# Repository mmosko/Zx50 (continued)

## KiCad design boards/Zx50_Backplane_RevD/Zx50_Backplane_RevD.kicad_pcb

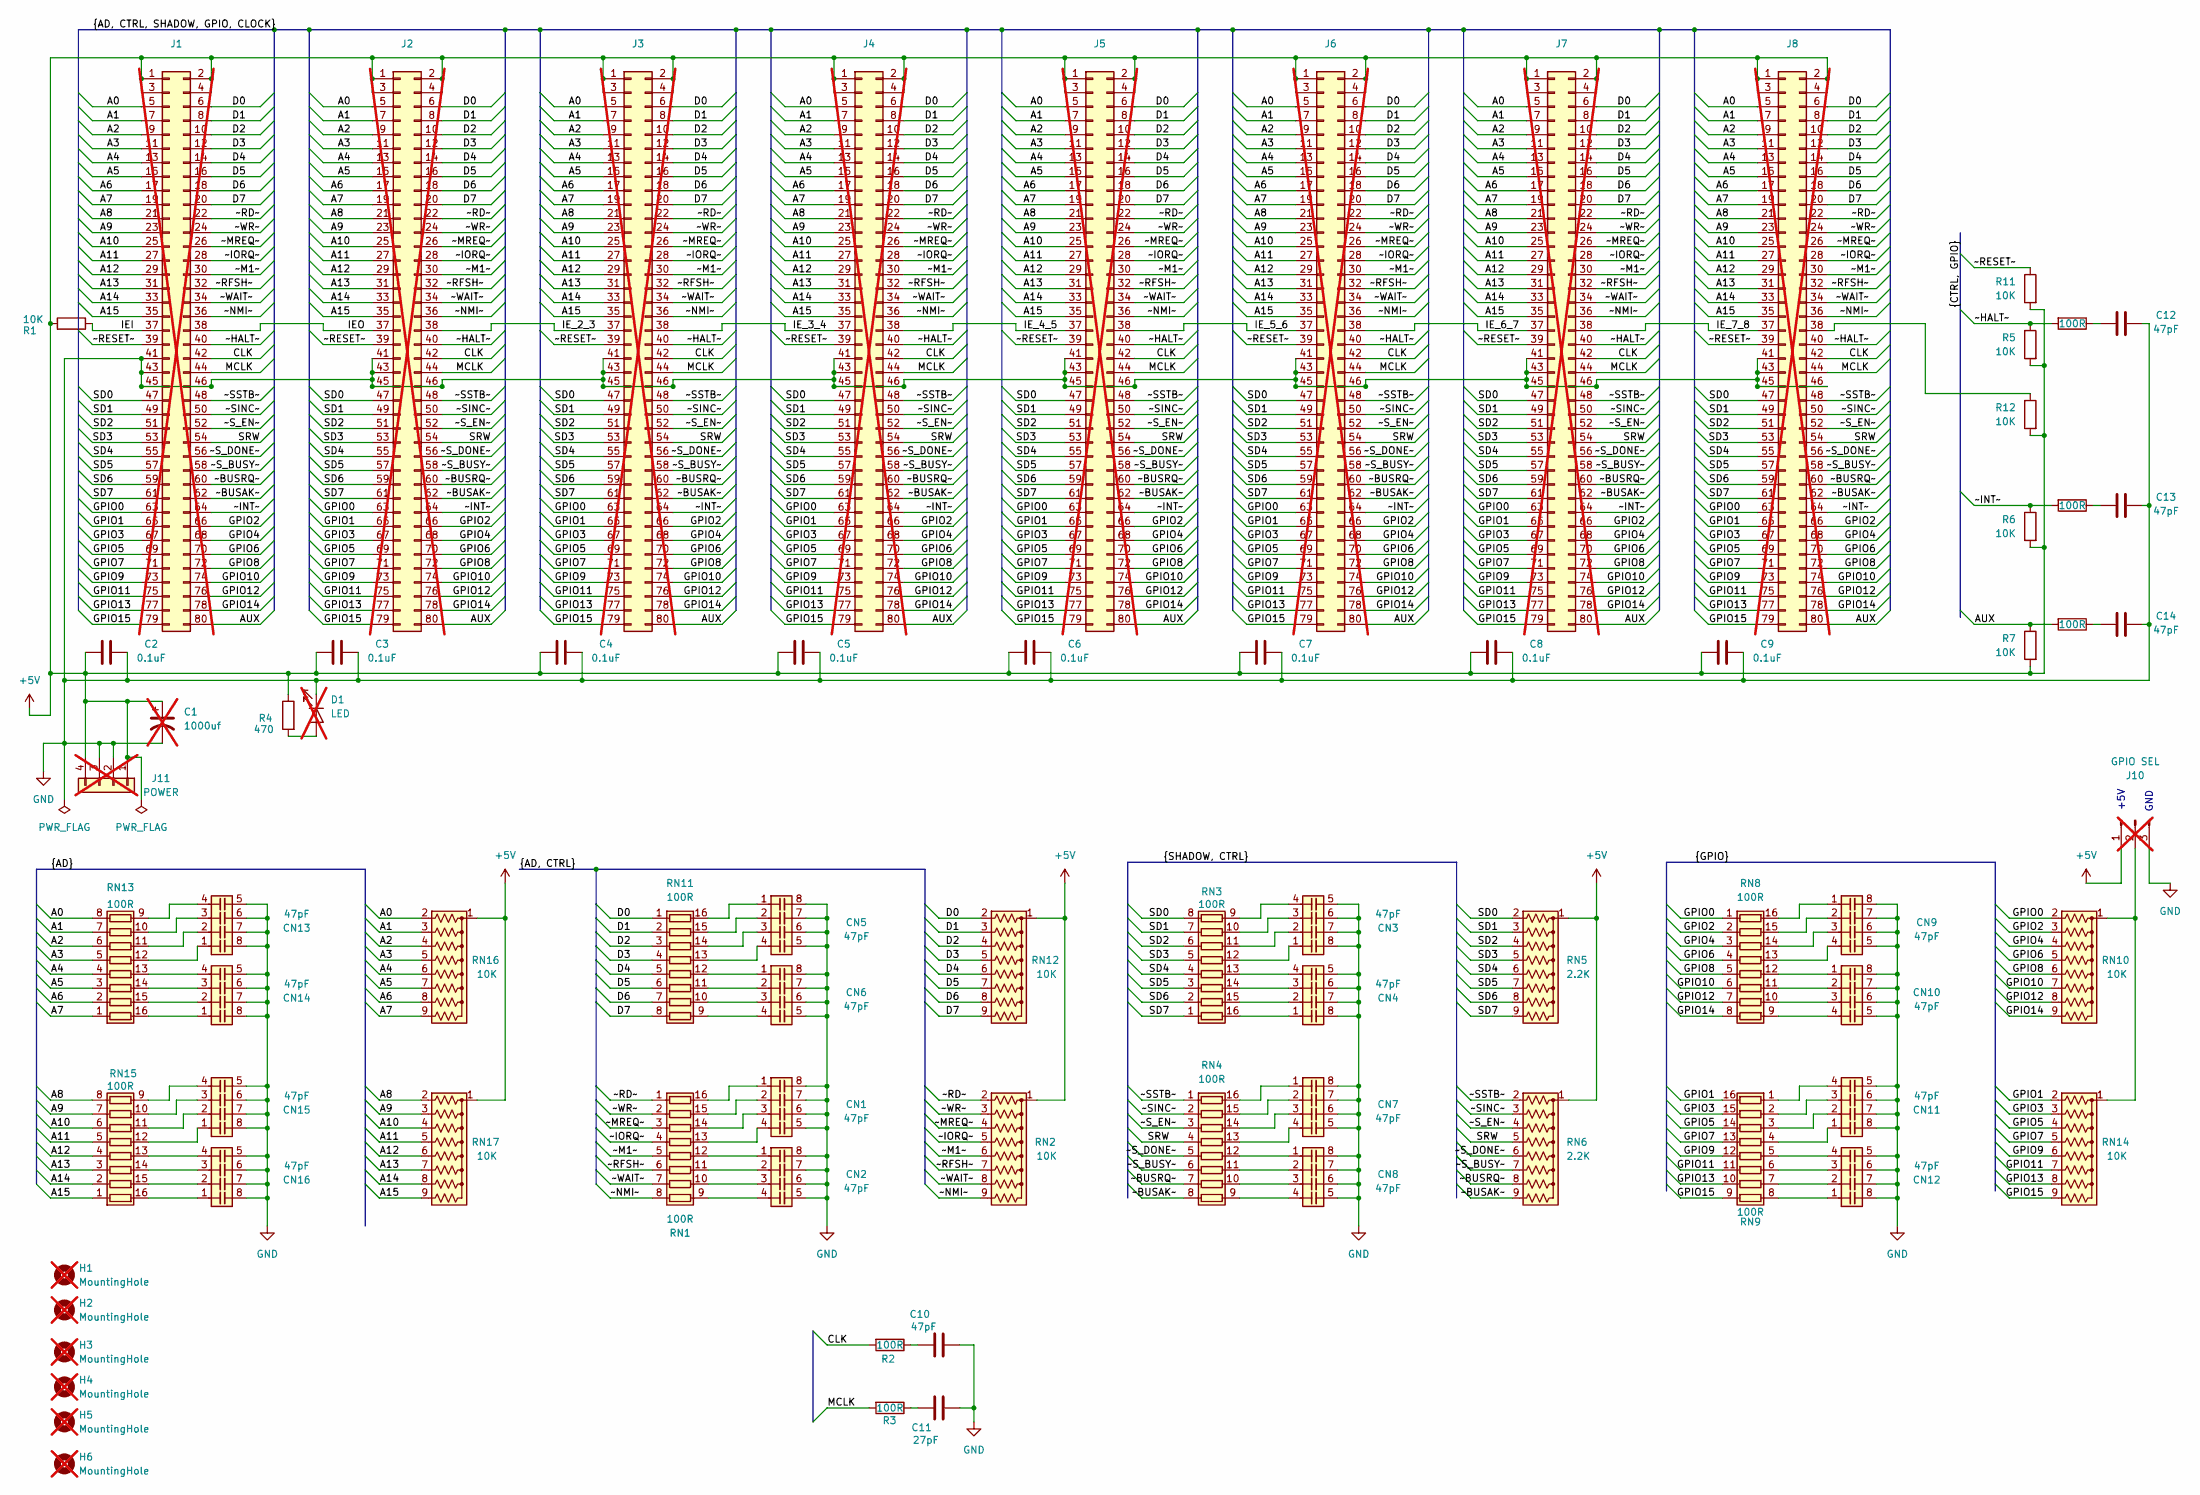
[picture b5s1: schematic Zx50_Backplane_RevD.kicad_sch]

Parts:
C1: 1000uf; CP_Radial_D10.0mm_P5.00mm; DigiKey_PN 493-15895-ND; not fitted
C2, C3, C4, C5, C6, C7, C8, C9: 0.1uF; C_0805_2012Metric; DigiKey_PN 399-C0805C104K5RACTUCT-ND
C10, C12, C13, C14: 47pF; C_0805_2012Metric; DigiKey_PN 399-C0805C101J5GACTUCT-ND
C11: 27pF; C_0805_2012Metric_Pad1.18x1.45mm_HandSolder; DigiKey_PN 478-600F270JT250XT4KCT-ND
CN1, CN2, CN3, CN4, CN5, CN6, CN7, CN8, CN9, CN10, CN11, CN12, CN13, CN14, CN15, CN16: 47pF; CAP_CA0612_3P2X1P6_YAG; DigiKey_PN 13-CA0612JRNPO9BN470CT-ND
D1: LED; LED_D5.0mm; DigiKey_PN 732-5016-ND; not fitted
H1, H2, H3, H4, H5, H6: MountingHole; MountingHole_3.2mm_M3; DigiKey_PN SJ5003-0-ND; not fitted
J1, J2, J3, J4, J5, J6, J7, J8: Conn_02x40_Odd_Even; PinSocket_2x40_P2.54mm_Vertical_Oval; DigiKey_PN SAM1179-40-ND; not fitted
J10: GPIO SEL; PinHeader_1x03_P2.54mm_Vertical; DigiKey_PN 732-5316-ND; not fitted
J11: POWER; TerminalBlock_Phoenix_MKDS-1,5-4-5.08_1x04_P5.08mm_Horizont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; DigiKey_PN 277-1238-ND; not fitted
R1, R5, R6, R7, R11, R12: 10K; R_0805_2012Metric_Pad1.20x1.40mm_HandSolder; DigiKey_PN RMCF0805FT10K0CT-ND
R2, R3, R8, R9, R10: 100R; R_0805_2012Metric; DigiKey_PN 311-100CRCT-ND
R4: 470; R_0805_2012Metric_Pad1.20x1.40mm_HandSolder; DigiKey_PN A130132CT-ND
RN1, RN3, RN4, RN8, RN9, RN11, RN13, RN15: 100R; SOIC-16W_5.3x10.2mm_P1.27mm; DigiKey_PN 4816P-1-101LFCT-ND
RN2, RN10, RN12, RN14, RN16, RN17: 10K; RN_9SRT_1_27mm_handsolder; DigiKey_PN 60-752091103GPTR7CT-ND
RN5, RN6: 2.2K; RN_9SRT_1_27mm_handsolder; DigiKey_PN 60-752091222GPTR7CT-ND

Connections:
+5V: C1.1, C2.1, C3.1, C4.1, C5.1, C6.1, C7.1, C8.1, C9.1, J1.1, J1.2, J1.3, J1.4, J2.1, J2.2, J2.3, J2.4, J3.1, J3.2, J3.3, J3.4, J4.1, J4.2, J4.3, J4.4, J5.1, J5.2, J5.3, J5.4, J6.1, J6.2, J6.3, J6.4, J7.1, J7.2, J7.3, J7.4, J8.1, J8.2, J8.3, J8.4, J10.1, J11.1, J11.4, R1.2, R4.1, R5.2, R6.2, R7.2, R11.2, R12.2, RN2.1 (common), RN5.1 (common), RN6.1 (common), RN12.1 (common), RN16.1 (common), RN17.1 (common)
/A0: J1.5, J2.5, J3.5, J4.5, J5.5, J6.5, J7.5, J8.5, RN13.8 (R8.1), RN16.2 (R1)
/A1: J1.7, J2.7, J3.7, J4.7, J5.7, J6.7, J7.7, J8.7, RN13.7 (R7.1), RN16.3 (R2)
/A2: J1.9, J2.9, J3.9, J4.9, J5.9, J6.9, J7.9, J8.9, RN13.6 (R6.1), RN16.4 (R3)
/A3: J1.11, J2.11, J3.11, J4.11, J5.11, J6.11, J7.11, J8.11, RN13.5 (R5.1), RN16.5 (R4)
/A4: J1.13, J2.13, J3.13, J4.13, J5.13, J6.13, J7.13, J8.13, RN13.4 (R4.1), RN16.6 (R5)
/A5: J1.15, J2.15, J3.15, J4.15, J5.15, J6.15, J7.15, J8.15, RN13.3 (R3.1), RN16.7 (R6)
/A6: J1.17, J2.17, J3.17, J4.17, J5.17, J6.17, J7.17, J8.17, RN13.2 (R2.1), RN16.8 (R7)
/A7: J1.19, J2.19, J3.19, J4.19, J5.19, J6.19, J7.19, J8.19, RN13.1 (R1.1), RN16.9 (R8)
/A8: J1.21, J2.21, J3.21, J4.21, J5.21, J6.21, J7.21, J8.21, RN15.8 (R8.1), RN17.2 (R1)
/A9: J1.23, J2.23, J3.23, J4.23, J5.23, J6.23, J7.23, J8.23, RN15.7 (R7.1), RN17.3 (R2)
/A10: J1.25, J2.25, J3.25, J4.25, J5.25, J6.25, J7.25, J8.25, RN15.6 (R6.1), RN17.4 (R3)
/A11: J1.27, J2.27, J3.27, J4.27, J5.27, J6.27, J7.27, J8.27, RN15.5 (R5.1), RN17.5 (R4)
/A12: J1.29, J2.29, J3.29, J4.29, J5.29, J6.29, J7.29, J8.29, RN15.4 (R4.1), RN17.6 (R5)
/A13: J1.31, J2.31, J3.31, J4.31, J5.31, J6.31, J7.31, J8.31, RN15.3 (R3.1), RN17.7 (R6)
/A14: J1.33, J2.33, J3.33, J4.33, J5.33, J6.33, J7.33, J8.33, RN15.2 (R2.1), RN17.8 (R7)
/A15: J1.35, J2.35, J3.35, J4.35, J5.35, J6.35, J7.35, J8.35, RN15.1 (R1.1), RN17.9 (R8)
/AUX: J1.80, J2.80, J3.80, J4.80, J5.80, J6.80, J7.80, J8.80, R7.1, R10.1
/CLK: J1.42, J2.42, J3.42, J4.42, J5.42, J6.42, J7.42, J8.42, R2.1
/D0: J1.6, J2.6, J3.6, J4.6, J5.6, J6.6, J7.6, J8.6, RN11.1 (R1.1), RN12.2 (R1)
/D1: J1.8, J2.8, J3.8, J4.8, J5.8, J6.8, J7.8, J8.8, RN11.2 (R2.1), RN12.3 (R2)
/D2: J1.10, J2.10, J3.10, J4.10, J5.10, J6.10, J7.10, J8.10, RN11.3 (R3.1), RN12.4 (R3)
/D3: J1.12, J2.12, J3.12, J4.12, J5.12, J6.12, J7.12, J8.12, RN11.4 (R4.1), RN12.5 (R4)
/D4: J1.14, J2.14, J3.14, J4.14, J5.14, J6.14, J7.14, J8.14, RN11.5 (R5.1), RN12.6 (R5)
/D5: J1.16, J2.16, J3.16, J4.16, J5.16, J6.16, J7.16, J8.16, RN11.6 (R6.1), RN12.7 (R6)
/D6: J1.18, J2.18, J3.18, J4.18, J5.18, J6.18, J7.18, J8.18, RN11.7 (R7.1), RN12.8 (R7)
/D7: J1.20, J2.20, J3.20, J4.20, J5.20, J6.20, J7.20, J8.20, RN11.8 (R8.1), RN12.9 (R8)
/GPIO0: J1.63, J2.63, J3.63, J4.63, J5.63, J6.63, J7.63, J8.63, RN8.1 (R1.1), RN10.2 (R1)
/GPIO1: J1.65, J2.65, J3.65, J4.65, J5.65, J6.65, J7.65, J8.65, RN9.16 (R1.2), RN14.2 (R1)
/GPIO2: J1.66, J2.66, J3.66, J4.66, J5.66, J6.66, J7.66, J8.66, RN8.2 (R2.1), RN10.3 (R2)
/GPIO3: J1.67, J2.67, J3.67, J4.67, J5.67, J6.67, J7.67, J8.67, RN9.15 (R2.2), RN14.3 (R2)
/GPIO4: J1.68, J2.68, J3.68, J4.68, J5.68, J6.68, J7.68, J8.68, RN8.3 (R3.1), RN10.4 (R3)
/GPIO5: J1.69, J2.69, J3.69, J4.69, J5.69, J6.69, J7.69, J8.69, RN9.14 (R3.2), RN14.4 (R3)
/GPIO6: J1.70, J2.70, J3.70, J4.70, J5.70, J6.70, J7.70, J8.70, RN8.4 (R4.1), RN10.5 (R4)
/GPIO7: J1.71, J2.71, J3.71, J4.71, J5.71, J6.71, J7.71, J8.71, RN9.13 (R4.2), RN14.5 (R4)
/GPIO8: J1.72, J2.72, J3.72, J4.72, J5.72, J6.72, J7.72, J8.72, RN8.5 (R5.1), RN10.6 (R5)
/GPIO9: J1.73, J2.73, J3.73, J4.73, J5.73, J6.73, J7.73, J8.73, RN9.12 (R5.2), RN14.6 (R5)
/GPIO10: J1.74, J2.74, J3.74, J4.74, J5.74, J6.74, J7.74, J8.74, RN8.6 (R6.1), RN10.7 (R6)
/GPIO11: J1.75, J2.75, J3.75, J4.75, J5.75, J6.75, J7.75, J8.75, RN9.11 (R6.2), RN14.7 (R6)
/GPIO12: J1.76, J2.76, J3.76, J4.76, J5.76, J6.76, J7.76, J8.76, RN8.7 (R7.1), RN10.8 (R7)
/GPIO13: J1.77, J2.77, J3.77, J4.77, J5.77, J6.77, J7.77, J8.77, RN9.10 (R7.2), RN14.8 (R7)
/GPIO14: J1.78, J2.78, J3.78, J4.78, J5.78, J6.78, J7.78, J8.78, RN8.8 (R8.1), RN10.9 (R8)
/GPIO15: J1.79, J2.79, J3.79, J4.79, J5.79, J6.79, J7.79, J8.79, RN9.9 (R8.2), RN14.9 (R8)
/IEI: J1.37, R1.1
/IEO: J1.38, J2.37
/IE_2_3: J2.38, J3.37
/IE_3_4: J3.38, J4.37
/IE_4_5: J4.38, J5.37
/IE_5_6: J5.38, J6.37
/IE_6_7: J6.38, J7.37
/IE_7_8: J7.38, J8.37
/MCLK: J1.44, J2.44, J3.44, J4.44, J5.44, J6.44, J7.44, J8.44, R3.1
/SD0: J1.47, J2.47, J3.47, J4.47, J5.47, J6.47, J7.47, J8.47, RN3.8 (R8.1), RN5.2 (R1)
/SD1: J1.49, J2.49, J3.49, J4.49, J5.49, J6.49, J7.49, J8.49, RN3.7 (R7.1), RN5.3 (R2)
/SD2: J1.51, J2.51, J3.51, J4.51, J5.51, J6.51, J7.51, J8.51, RN3.6 (R6.1), RN5.4 (R3)
/SD3: J1.53, J2.53, J3.53, J4.53, J5.53, J6.53, J7.53, J8.53, RN3.5 (R5.1), RN5.5 (R4)
/SD4: J1.55, J2.55, J3.55, J4.55, J5.55, J6.55, J7.55, J8.55, RN3.4 (R4.1), RN5.6 (R5)
/SD5: J1.57, J2.57, J3.57, J4.57, J5.57, J6.57, J7.57, J8.57, RN3.3 (R3.1), RN5.7 (R6)
/SD6: J1.59, J2.59, J3.59, J4.59, J5.59, J6.59, J7.59, J8.59, RN3.2 (R2.1), RN5.8 (R7)
/SD7: J1.61, J2.61, J3.61, J4.61, J5.61, J6.61, J7.61, J8.61, RN3.1 (R1.1), RN5.9 (R8)
/SRW: J1.54, J2.54, J3.54, J4.54, J5.54, J6.54, J7.54, J8.54, RN4.4 (R4.1), RN6.5 (R4)
/~BUSAK~: J1.62, J2.62, J3.62, J4.62, J5.62, J6.62, J7.62, J8.62, RN4.8 (R8.1), RN6.9 (R8)
/~BUSRQ~: J1.60, J2.60, J3.60, J4.60, J5.60, J6.60, J7.60, J8.60, RN4.7 (R7.1), RN6.8 (R7)
/~HALT~: J1.40, J2.40, J3.40, J4.40, J5.40, J6.40, J7.40, J8.40, R5.1, R8.1
/~INT~: J1.64, J2.64, J3.64, J4.64, J5.64, J6.64, J7.64, J8.64, R6.1, R9.1
/~IORQ~: J1.28, J2.28, J3.28, J4.28, J5.28, J6.28, J7.28, J8.28, RN1.4 (R4.1), RN2.5 (R4)
/~M1~: J1.30, J2.30, J3.30, J4.30, J5.30, J6.30, J7.30, J8.30, RN1.5 (R5.1), RN2.6 (R5)
/~MREQ~: J1.26, J2.26, J3.26, J4.26, J5.26, J6.26, J7.26, J8.26, RN1.3 (R3.1), RN2.4 (R3)
/~NMI~: J1.36, J2.36, J3.36, J4.36, J5.36, J6.36, J7.36, J8.36, RN1.8 (R8.1), RN2.9 (R8)
/~RD~: J1.22, J2.22, J3.22, J4.22, J5.22, J6.22, J7.22, J8.22, RN1.1 (R1.1), RN2.2 (R1)
/~RESET~: J1.39, J2.39, J3.39, J4.39, J5.39, J6.39, J7.39, J8.39, R11.1
/~RFSH~: J1.32, J2.32, J3.32, J4.32, J5.32, J6.32, J7.32, J8.32, RN1.6 (R6.1), RN2.7 (R6)
/~SINC~: J1.50, J2.50, J3.50, J4.50, J5.50, J6.50, J7.50, J8.50, RN4.2 (R2.1), RN6.3 (R2)
/~SSTB~: J1.48, J2.48, J3.48, J4.48, J5.48, J6.48, J7.48, J8.48, RN4.1 (R1.1), RN6.2 (R1)
/~S_BUSY~: J1.58, J2.58, J3.58, J4.58, J5.58, J6.58, J7.58, J8.58, RN4.6 (R6.1), RN6.7 (R6)
/~S_DONE~: J1.56, J2.56, J3.56, J4.56, J5.56, J6.56, J7.56, J8.56, RN4.5 (R5.1), RN6.6 (R5)
/~S_EN~: J1.52, J2.52, J3.52, J4.52, J5.52, J6.52, J7.52, J8.52, RN4.3 (R3.1), RN6.4 (R3)
/~WAIT~: J1.34, J2.34, J3.34, J4.34, J5.34, J6.34, J7.34, J8.34, RN1.7 (R7.1), RN2.8 (R7)
/~WR~: J1.24, J2.24, J3.24, J4.24, J5.24, J6.24, J7.24, J8.24, RN1.2 (R2.1), RN2.3 (R2)
GND: C1.2, C2.2, C3.2, C4.2, C5.2, C6.2, C7.2, C8.2, C9.2, C10.2, C11.1, C12.2, C13.2, C14.2, CN1.5 (C4), CN1.6 (C3), CN1.7 (C2), CN1.8 (C1), CN2.5 (C4), CN2.6 (C3), CN2.7 (C2), CN2.8 (C1), CN3.5 (C4), CN3.6 (C3), CN3.7 (C2), CN3.8 (C1), CN4.5 (C4), CN4.6 (C3), CN4.7 (C2), CN4.8 (C1), CN5.5 (C4), CN5.6 (C3), CN5.7 (C2), CN5.8 (C1), CN6.5 (C4), CN6.6 (C3), CN6.7 (C2), CN6.8 (C1), CN7.5 (C4), CN7.6 (C3), CN7.7 (C2), CN7.8 (C1), CN8.5 (C4), CN8.6 (C3), CN8.7 (C2), CN8.8 (C1), CN9.5 (C4), CN9.6 (C3), CN9.7 (C2), CN9.8 (C1), CN10.5 (C4), CN10.6 (C3), CN10.7 (C2), CN10.8 (C1), CN11.5 (C4), CN11.6 (C3), CN11.7 (C2), CN11.8 (C1), CN12.5 (C4), CN12.6 (C3), CN12.7 (C2), CN12.8 (C1), CN13.5 (C4), CN13.6 (C3), CN13.7 (C2), CN13.8 (C1), CN14.5 (C4), CN14.6 (C3), CN14.7 (C2), CN14.8 (C1), CN15.5 (C4), CN15.6 (C3), CN15.7 (C2), CN15.8 (C1), CN16.5 (C4), CN16.6 (C3), CN16.7 (C2), CN16.8 (C1), D1.1 (K), J1.41, J1.43, J1.45, J1.46, J2.41, J2.43, J2.45, J2.46, J3.41, J3.43, J3.45, J3.46, J4.41, J4.43, J4.45, J4.46, J5.41, J5.43, J5.45, J5.46, J6.41, J6.43, J6.45, J6.46, J7.41, J7.43, J7.45, J7.46, J8.41, J8.43, J8.45, J8.46, J10.3, J11.2, J11.3
unnamed: C10.1, R2.2
unnamed: C11.2, R3.2
unnamed: C12.1, R8.2
unnamed: C13.1, R9.2
unnamed: C14.1, R10.2
unnamed: D1.2 (A), R4.2
unnamed: J8.38, R12.1
unnamed: J10.2, RN10.1 (common), RN14.1 (common)
unnamed: CN1.1 (common), RN1.16 (R1.2)
unnamed: CN1.2 (common), RN1.15 (R2.2)
unnamed: CN1.3 (common), RN1.14 (R3.2)
unnamed: CN1.4 (common), RN1.13 (R4.2)
unnamed: CN2.1 (common), RN1.12 (R5.2)
unnamed: CN2.2 (common), RN1.11 (R6.2)
unnamed: CN2.3 (common), RN1.10 (R7.2)
unnamed: CN2.4 (common), RN1.9 (R8.2)
unnamed: CN4.1 (common), RN3.16 (R1.2)
unnamed: CN4.2 (common), RN3.15 (R2.2)
unnamed: CN4.3 (common), RN3.14 (R3.2)
unnamed: CN4.4 (common), RN3.13 (R4.2)
unnamed: CN3.1 (common), RN3.12 (R5.2)
unnamed: CN3.2 (common), RN3.11 (R6.2)
unnamed: CN3.3 (common), RN3.10 (R7.2)
unnamed: CN3.4 (common), RN3.9 (R8.2)
unnamed: CN7.1 (common), RN4.16 (R1.2)
unnamed: CN7.2 (common), RN4.15 (R2.2)
unnamed: CN7.3 (common), RN4.14 (R3.2)
unnamed: CN7.4 (common), RN4.13 (R4.2)
unnamed: CN8.1 (common), RN4.12 (R5.2)
unnamed: CN8.2 (common), RN4.11 (R6.2)
unnamed: CN8.3 (common), RN4.10 (R7.2)
unnamed: CN8.4 (common), RN4.9 (R8.2)
unnamed: CN9.1 (common), RN8.16 (R1.2)
unnamed: CN9.2 (common), RN8.15 (R2.2)
unnamed: CN9.3 (common), RN8.14 (R3.2)
unnamed: CN9.4 (common), RN8.13 (R4.2)
unnamed: CN10.1 (common), RN8.12 (R5.2)
unnamed: CN10.2 (common), RN8.11 (R6.2)
unnamed: CN10.3 (common), RN8.10 (R7.2)
unnamed: CN10.4 (common), RN8.9 (R8.2)
unnamed: CN11.4 (common), RN9.1 (R1.1)
unnamed: CN11.3 (common), RN9.2 (R2.1)
unnamed: CN11.2 (common), RN9.3 (R3.1)
unnamed: CN11.1 (common), RN9.4 (R4.1)
unnamed: CN12.4 (common), RN9.5 (R5.1)
unnamed: CN12.3 (common), RN9.6 (R6.1)
unnamed: CN12.2 (common), RN9.7 (R7.1)
unnamed: CN12.1 (common), RN9.8 (R8.1)
unnamed: CN5.1 (common), RN11.16 (R1.2)
unnamed: CN5.2 (common), RN11.15 (R2.2)
unnamed: CN5.3 (common), RN11.14 (R3.2)
unnamed: CN5.4 (common), RN11.13 (R4.2)
unnamed: CN6.1 (common), RN11.12 (R5.2)
unnamed: CN6.2 (common), RN11.11 (R6.2)
unnamed: CN6.3 (common), RN11.10 (R7.2)
unnamed: CN6.4 (common), RN11.9 (R8.2)
unnamed: CN14.1 (common), RN13.16 (R1.2)
unnamed: CN14.2 (common), RN13.15 (R2.2)
unnamed: CN14.3 (common), RN13.14 (R3.2)
unnamed: CN14.4 (common), RN13.13 (R4.2)
unnamed: CN13.1 (common), RN13.12 (R5.2)
unnamed: CN13.2 (common), RN13.11 (R6.2)
unnamed: CN13.3 (common), RN13.10 (R7.2)
unnamed: CN13.4 (common), RN13.9 (R8.2)
unnamed: CN16.1 (common), RN15.16 (R1.2)
unnamed: CN16.2 (common), RN15.15 (R2.2)
unnamed: CN16.3 (common), RN15.14 (R3.2)
unnamed: CN16.4 (common), RN15.13 (R4.2)
unnamed: CN15.1 (common), RN15.12 (R5.2)
unnamed: CN15.2 (common), RN15.11 (R6.2)
unnamed: CN15.3 (common), RN15.10 (R7.2)
unnamed: CN15.4 (common), RN15.9 (R8.2)

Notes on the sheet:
+5V
GND

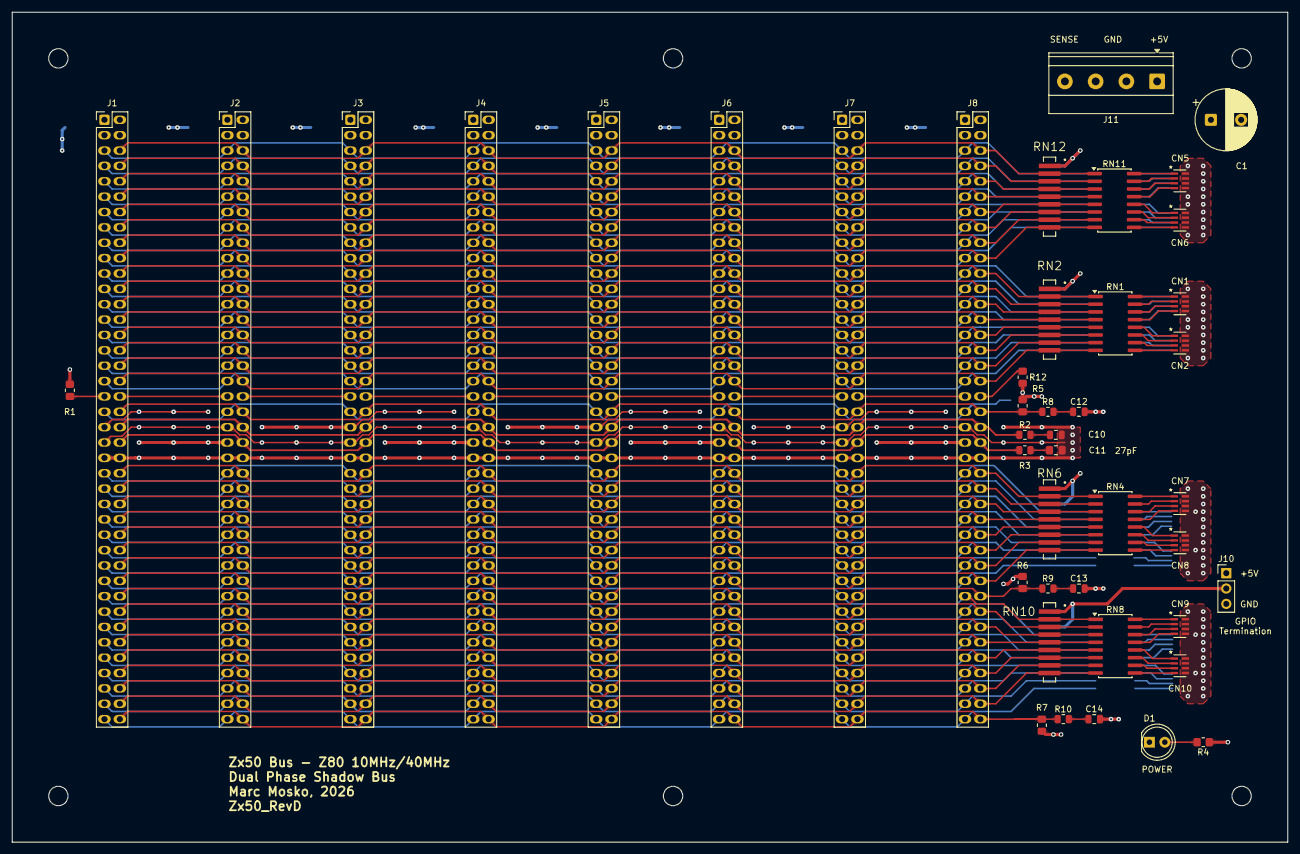
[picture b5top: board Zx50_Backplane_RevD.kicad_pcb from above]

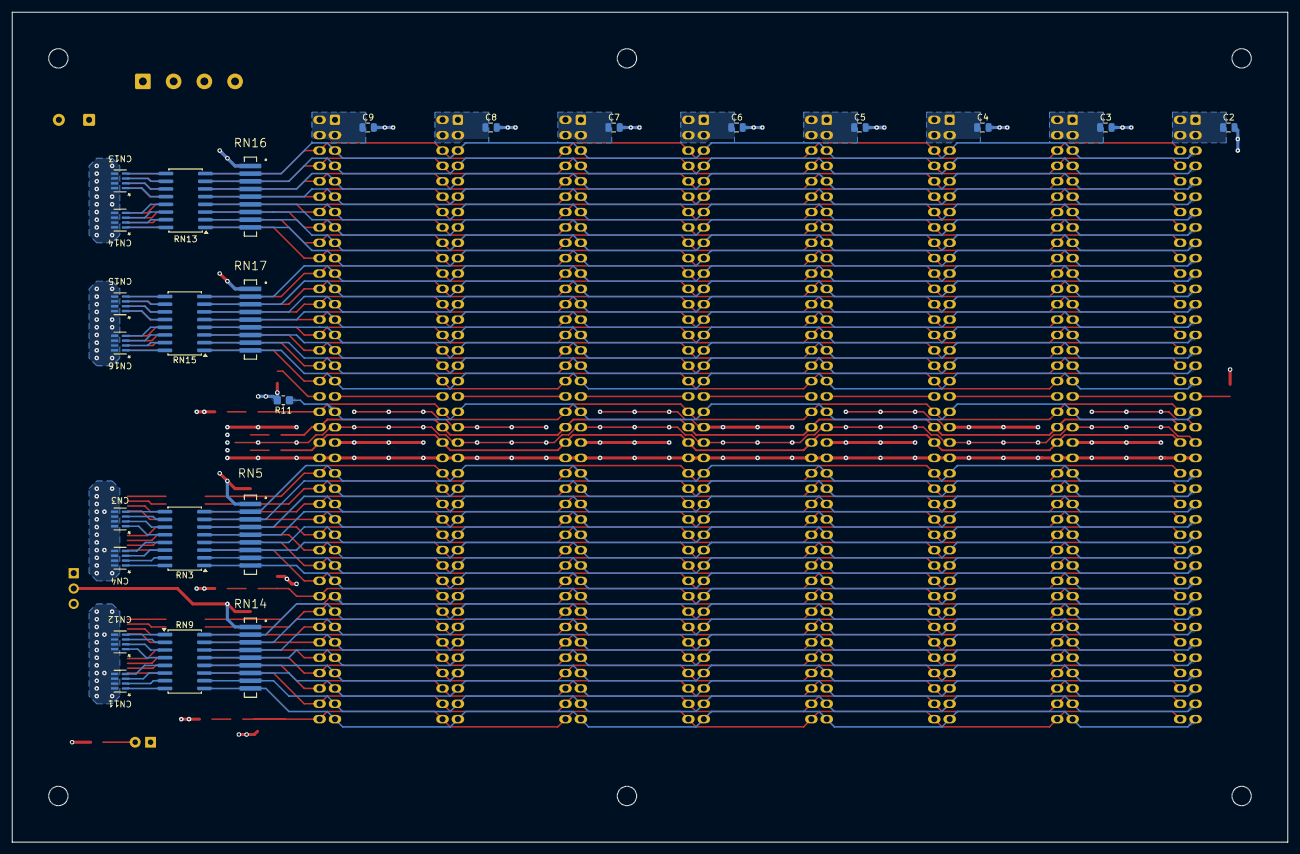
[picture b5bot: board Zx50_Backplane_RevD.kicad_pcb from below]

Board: 4 copper layers, 210.8 x 137.2 mm, 75 parts (25 on the bottom side), 152 nets.

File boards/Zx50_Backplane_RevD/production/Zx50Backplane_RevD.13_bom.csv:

Designator,Footprint,Quantity,Value,LCSC Part #
"C10, C12, C13, C14",0805,4,47pF,C14857
C11,0805,1,27pF,C49326673
"C2, C3, C4, C5, C6, C7, C8, C9",0805,8,0.1uF,C28233
"CN1, CN10, CN11, CN12, CN13, CN14, CN15, CN16, CN2, CN3, CN4, CN5, CN6, CN7, CN8, CN9",CAP_CA0612_3P2X1P6_YAG,16,47pF,C22446551
"R1, R11, R12, R5, R6, R7",0805,6,10K,C237755
"R10, R2, R3, R8, R9",0805,5,100R,C17408
R4,0805,1,470,C17710
"RN1, RN11, RN13, RN15, RN3, RN4, RN8, RN9",SOIC-16W_5.3x10.2mm_P1.27mm,8,100R,C1358123
"RN10, RN12, RN14, RN16, RN17, RN2",RN_9SRT_1_27mm_handsolder,6,10K,C7193336
"RN5, RN6",RN_9SRT_1_27mm_handsolder,2,2.2K,C1731646

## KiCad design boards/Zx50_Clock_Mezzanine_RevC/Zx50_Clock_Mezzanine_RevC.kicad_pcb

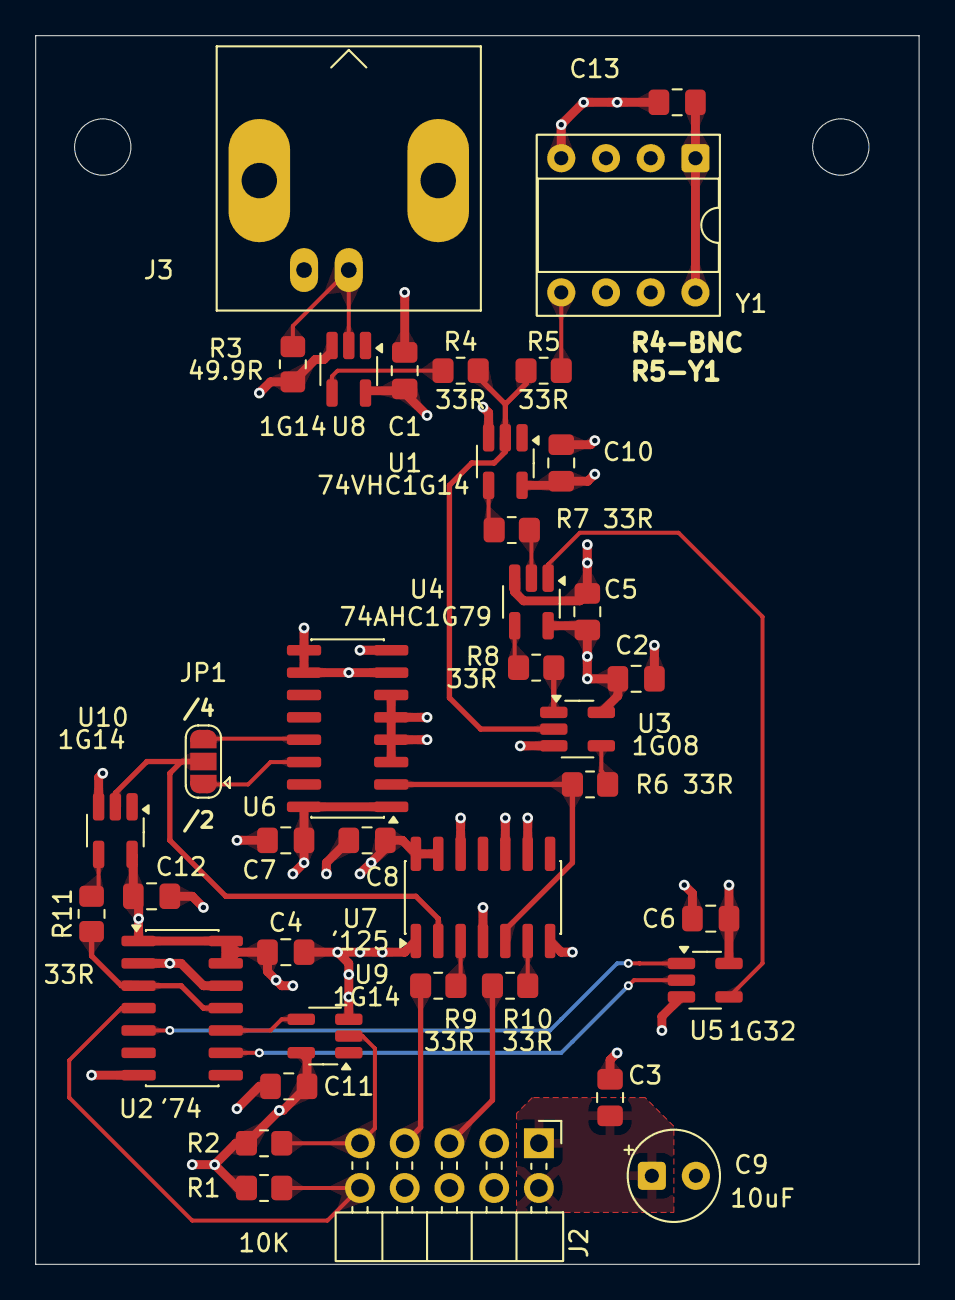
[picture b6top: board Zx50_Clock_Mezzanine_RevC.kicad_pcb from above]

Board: 4 copper layers, 50.2 x 69.8 mm, 38 parts (0 on the bottom side), 27 nets.

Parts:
C1, C10, C11, C12, C13: 0.1 uF; C_0805_2012Metric_Pad1.18x1.45mm_HandSolder
C2, C3, C4, C5, C6, C7, C8: 0.1uF; C_0805_2012Metric_Pad1.18x1.45mm_HandSolder
C9: 10uF; CP_Radial_Tantal_D5.0mm_P2.50mm
J2: Conn_02x05_Odd_Even; PinHeader_2x05_P2.54mm_Horizontal_Edge
J3: Conn_Coaxial; BNC_Amphenol_B6252HB-NPP3G-50_Horizontal
JP1: CLOCK DIV; SolderJumper-3_P1.3mm_Open_RoundedPad1.0x1.5mm
R1, R2: 10K; R_0805_2012Metric_Pad1.20x1.40mm_HandSolder
R3: 49.9R; R_0805_2012Metric_Pad1.20x1.40mm_HandSolder
R4, R5, R6, R7, R8, R9, R10, R11: 33R; R_0805_2012Metric_Pad1.20x1.40mm_HandSolder
U1: 74VHC1G14; SOT-23-5_HandSoldering
U2: '74; SOIC-14_3.9x8.7mm_P1.27mm
U3: 1G08; SOT-23-5_HandSoldering
U4: 74AHC1G79; SOT-23-5_HandSoldering
U5: 1G32; SOT-23-5_HandSoldering
U6: CD74AC161M96; SOIC-16_3.9x9.9mm_P1.27mm
U7: '125; SOIC-14_3.9x8.7mm_P1.27mm
U8, U9, U10: 1G14; SOT-23-5_HandSoldering
Y1: SG-8002DC; DIP-8_W7.62mm_Socket

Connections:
+5V: C1.1, C2.1, C3.1, C4.1, C5.1, C6.1, C7.1, C8.1, C9.1, C10.1, C11.1, C12.1, C13.1, J2.1, J2.2, R1.1, R2.1, U1.5 (VCC), U2.1 (1~CLR), U2.13 (2~CLR), U2.14 (VCC), U3.5 (VCC), U4.5 (VCC), U5.5 (VCC), U6.1 (~CLR), U6.7 (ENP), U6.9 (~LOAD), U6.10 (ENT), U6.16 (VCC), U7.13 (4~OE), U7.14 (VCC), U8.5 (VCC), U9.5 (VCC), U10.5 (VCC), Y1.1 (OE), Y1.8 (Vcc)
/AFG_EXT_IN: J3.1 (In), R3.1, U8.2 (IN_A)
/ASYNC_REQ: U4.1 (D), U5.4
/DIV_2: JP1.1 (A), U6.14 (QA)
/DIV_4: JP1.3 (B), U6.13 (QB)
/MCLK_EN_SAFE: R8.1, U3.1
/MCLK_INT: R6.2, U6.2 (CLK), U7.5 (2A)
/MCLK_OUT: J2.5, R10.2
/MCLK_RAW: R4.2, R5.1, U1.2 (IN_A), U3.2
/RUN_IN: J2.9, R2.2, U9.2 (IN_A)
/RUN_SYNC: U2.9 (2Q), U5.2
/STEP_N_IN: J2.10, R1.2, U2.4 (1~PRE)
/STEP_SYNC: U2.5 (1Q), U5.1
/ZCLK_INT: JP1.2 (C), U7.2 (1A), U10.2 (IN_A)
/ZCLK_OUT: J2.7, R9.2
/~MCLK_RAW: R7.2, U4.2 (CLK)
/~RUN_IN: U2.10 (2~PRE), U9.4 (OUT~Y)
/~ZCLK_INT: R11.1, U2.3 (1CLK), U2.11 (2CLK)
GND: C1.2, C2.2, C3.2, C4.2, C5.2, C6.2, C7.2, C8.2, C9.2, C10.2, C11.2, C12.2, C13.2, J2.3, J2.4, J2.6, J2.8, J3.2 (Ext), R3.2, U1.3 (GND), U2.2 (1D), U2.7 (GND), U2.12 (2D), U3.3 (GND), U4.3 (GND), U5.3 (GND), U6.3 (A), U6.4 (B), U6.5 (C), U6.6 (D), U6.8 (GND), U7.1 (1~OE), U7.4 (2~OE), U7.7 (GND), U7.9 (3A), U7.10 (3~OE), U7.12 (4A), U8.3 (GND), U9.3 (GND), U10.3 (GND), Y1.4 (GND)
unnamed: R6.1, U3.4
unnamed: R7.1, U1.4 (OUT~Y)
unnamed: R8.2, U4.4 (Q)
unnamed: R9.1, U7.3 (1Y)
unnamed: R10.1, U7.6 (2Y)
unnamed: R4.1, U8.4 (OUT~Y)
unnamed: R11.2, U10.4 (OUT~Y)
unnamed: R5.2, Y1.5 (OUT)

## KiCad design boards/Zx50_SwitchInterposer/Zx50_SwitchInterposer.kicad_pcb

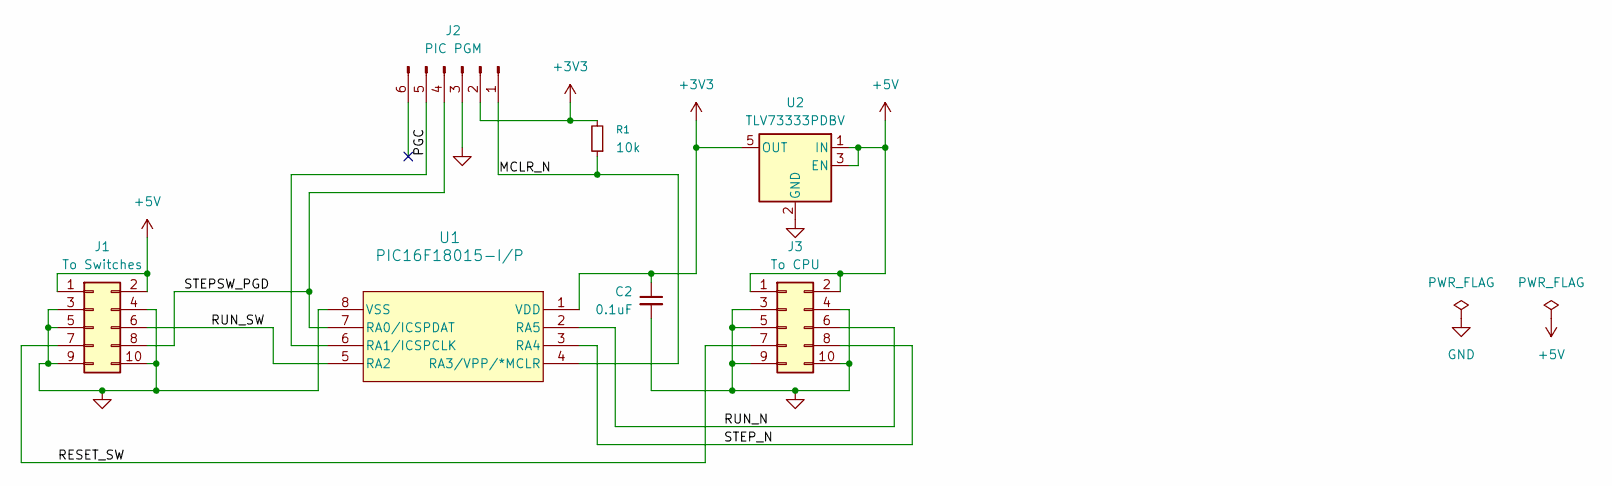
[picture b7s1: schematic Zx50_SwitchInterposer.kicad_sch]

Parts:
C2: 0.1uF; C_Disc_D5.0mm_W2.5mm_P5.00mm; DigiKey_PN BC1101CT-ND
J1: To Switches; PinSocket_2x05_P2.54mm_Vertical; DigiKey_PN S9194-ND
J2: PIC PGM; PinHeader_1x06_P2.54mm_Horizontal_EDGE; Digi-Key_PN 732-5339-ND
J3: To CPU; IDC-Header_2x05_P2.54mm_Vertical; DigiKey_PN 732-2098-ND
R1: 10k; R_Axial_DIN0207_L6.3mm_D2.5mm_P10.16mm_Horizontal
U1: PIC16F18015-I/P; DIP-8_W7.62mm; DigiKey_PN 150-PIC16F18015-I/P-ND
U2: TLV73333PDBV; SOT-23-5

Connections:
+3V3: C2.1, J2.2, R1.2, U1.1 (VDD), U2.5 (OUT)
+5V: J1.1, J1.2, J3.1, J3.2, U2.1 (IN), U2.3 (EN)
/MCLR_N: J2.1, R1.1, U1.4 (RA3/VPP/*MCLR)
/PGC: J2.5, U1.6 (RA1/ICSPCLK)
/RESET_SW: J1.7, J3.7
/RUN_N: J3.6, U1.2 (RA5)
/RUN_SW: J1.6, U1.5 (RA2)
/STEPSW_PGD: J1.8, J2.4, U1.7 (RA0/ICSPDAT)
/STEP_N: J3.8, U1.3 (RA4)
GND: C2.2, J1.3, J1.4, J1.5, J1.9, J1.10, J2.3, J3.3, J3.4, J3.5, J3.9, J3.10, U1.8 (VSS), U2.2 (GND)

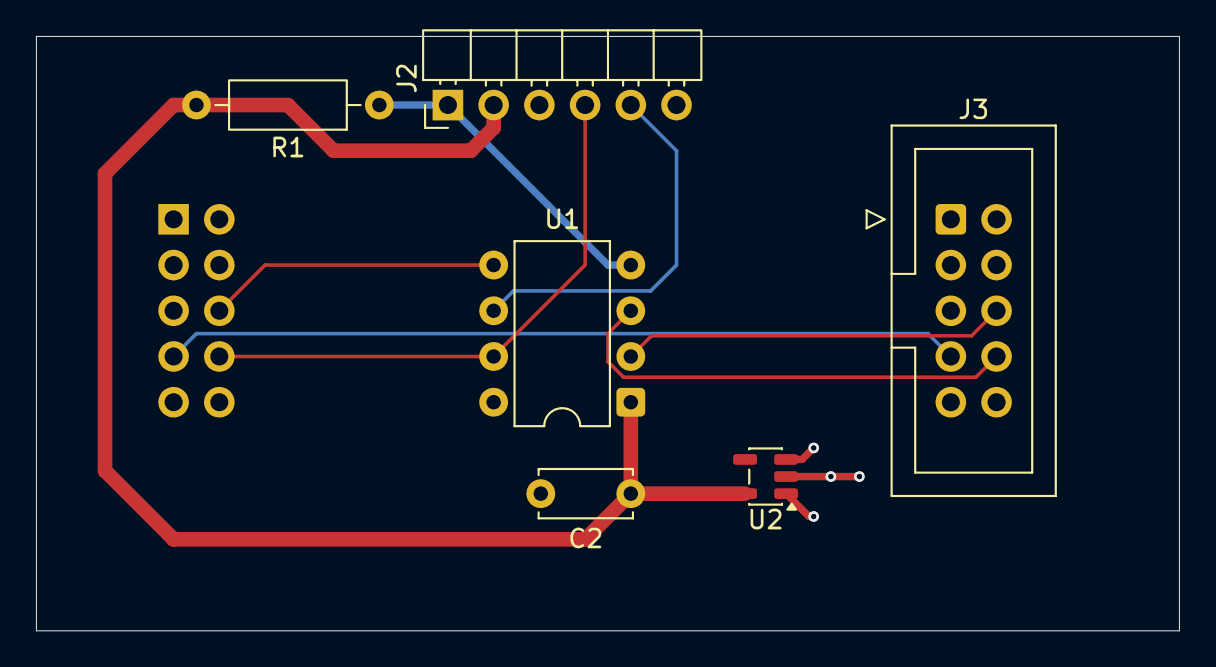
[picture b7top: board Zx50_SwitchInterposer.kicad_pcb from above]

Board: 4 copper layers, 63.5 x 33.0 mm, 7 parts (1 on the bottom side), 10 nets.

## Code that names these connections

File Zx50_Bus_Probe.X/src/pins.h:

/* 
 * File:   pins.h
 * Author: Marc Mosko
 * Description: Hardware Abstraction Layer for Zx50 Bus Probe Rev A.
 * Defines meaningful names for all PIC18F4620 I/O pins based on schematic nets.
 */

#ifndef PINS_H
#define	PINS_H

#include <xc.h>

// ==========================================
// Z80 DATA BUS (Transceiver U6)
// ==========================================
// Directly connected to PORTD
// Control the DIRection, the LATch, and the VALue
#define Z80_DATA_DIR       TRISD
#define Z80_DATA_LAT       LATD
#define Z80_DATA_VAL       PORTD

// ==========================================
// TRANSCEIVER CONTROLS (U6 Data, U7 Control)
// ==========================================
// U7 Control Transceiver
#define XCVR_CTRL_OE_DIR   TRISAbits.TRISA0
#define XCVR_CTRL_OE_LAT   LATAbits.LATA0
#define XCVR_CTRL_DIR_DIR  TRISAbits.TRISA1
#define XCVR_CTRL_DIR_LAT  LATAbits.LATA1

// U6 Data Transceiver
#define XCVR_DATA_OE_DIR   TRISAbits.TRISA2
#define XCVR_DATA_OE_LAT   LATAbits.LATA2
#define XCVR_DATA_DIR_DIR  TRISAbits.TRISA3
#define XCVR_DATA_DIR_LAT  LATAbits.LATA3

// ==========================================
// Z80 CONTROL BUS (Via U7 Transceiver)
// ==========================================
#define Z80_RD_DIR         TRISBbits.TRISB5
#define Z80_RD_LAT         LATBbits.LATB5

#define Z80_WR_DIR         TRISEbits.TRISE0
#define Z80_WR_LAT         LATEbits.LATE0

#define Z80_MREQ_DIR       TRISBbits.TRISB3
#define Z80_MREQ_LAT       LATBbits.LATB3

#define Z80_IORQ_DIR       TRISBbits.TRISB4
#define Z80_IORQ_LAT       LATBbits.LATB4

#define Z80_M1_DIR         TRISEbits.TRISE1
#define Z80_M1_LAT         LATEbits.LATE1

#define Z80_RESET_DIR      TRISEbits.TRISE2
#define Z80_RESET_LAT      LATEbits.LATE2

// ==========================================
// Z80 DIRECT INPUTS (Bypassing Transceivers)
// ==========================================
#define Z80_INT_DIR        TRISBbits.TRISB0
#define Z80_INT_VAL        PORTBbits.RB0

#define Z80_WAIT_DIR       TRISBbits.TRISB1
#define Z80_WAIT_VAL       PORTBbits.RB1

// ==========================================
// SPI & EXPANDER CONTROLS (U1, U13)
// ==========================================
#define EXP_RESET_DIR      TRISAbits.TRISA4
#define EXP_RESET_LAT      LATAbits.LATA4

#define SPI_CS_DIR         TRISAbits.TRISA5
#define SPI_CS_LAT         LATAbits.LATA5

// SPI Hardware Pins (Managed by SSP Module, but good to define)
#define SPI_SCK_DIR        TRISCbits.TRISC3
#define SPI_SDI_DIR        TRISCbits.TRISC4
#define SPI_SDO_DIR        TRISCbits.TRISC5

// ==========================================
// UART COMMUNICATON
// ==========================================
// UART Hardware Pins (Managed by EUSART Module)
#define UART_TX_DIR        TRISCbits.TRISC6
#define UART_RX_DIR        TRISCbits.TRISC7

// ==========================================
// CLOCKS & AUXILIARY
// ==========================================
#define AUX_PIN_DIR        TRISCbits.TRISC0
#define AUX_PIN_LAT        LATCbits.LATC0
#define AUX_PIN_VAL        PORTCbits.RC0

#define MCLK_PIN_DIR       TRISCbits.TRISC1
#define MCLK_PIN_LAT       LATCbits.LATC1

#define CLK_PIN_DIR        TRISCbits.TRISC2
#define CLK_PIN_LAT        LATCbits.LATC2

// ==========================================
// SHADOW RAM CONTROLS
// ==========================================
#define SHADOW_BUSY_DIR    TRISBbits.TRISB2
#define SHADOW_BUSY_VAL    PORTBbits.RB2

#endif	/* PINS_H */

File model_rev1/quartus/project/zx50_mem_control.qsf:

# -------------------------------------------------------------------------- #
#
# Copyright (C) 1991-2013 Altera Corporation
# Your use of Altera Corporation's design tools, logic functions 
# and other software and tools, and its AMPP partner logic 
# functions, and any output files from any of the foregoing 
# (including device programming or simulation files), and any 
# associated documentation or information are expressly subject 
# to the terms and conditions of the Altera Program License 
# Subscription Agreement, Altera MegaCore Function License 
# Agreement, or other applicable license agreement, including, 
# without limitation, that your use is for the sole purpose of 
# programming logic devices manufactured by Altera and sold by 
# Altera or its authorized distributors.  Please refer to the 
# applicable agreement for further details.
#
# -------------------------------------------------------------------------- #
#
# Quartus II 64-Bit
# Version 13.0.1 Build 232 06/12/2013 Service Pack 1 SJ Web Edition
# Date created = 09:43:06  April 23, 2026
#
# -------------------------------------------------------------------------- #
#
# Notes:
#
# 1) The default values for assignments are stored in the file:
#		zx50_mem_control_assignment_defaults.qdf
#    If this file doesn't exist, see file:
#		assignment_defaults.qdf
#
# 2) Altera recommends that you do not modify this file. This
#    file is updated automatically by the Quartus II software
#    and any changes you make may be lost or overwritten.
#
# -------------------------------------------------------------------------- #


set_global_assignment -name FAMILY MAX7000S
set_global_assignment -name DEVICE "EPM7128STC100-15"
set_global_assignment -name TOP_LEVEL_ENTITY zx50_mem_control
set_global_assignment -name ORIGINAL_QUARTUS_VERSION "13.0 SP1"
set_global_assignment -name PROJECT_CREATION_TIME_DATE "09:43:06  APRIL 23, 2026"
set_global_assignment -name LAST_QUARTUS_VERSION "13.0 SP1"
set_global_assignment -name PROJECT_OUTPUT_DIRECTORY output_files
set_global_assignment -name DEVICE_FILTER_PIN_COUNT 100
set_global_assignment -name ERROR_CHECK_FREQUENCY_DIVISOR "-1"
set_global_assignment -name EDA_SIMULATION_TOOL "ModelSim-Altera (VHDL)"
set_global_assignment -name EDA_OUTPUT_DATA_FORMAT VHDL -section_id eda_simulation
set_global_assignment -name MAX7000_OPTIMIZATION_TECHNIQUE AREA
set_global_assignment -name SYNTH_TIMING_DRIVEN_SYNTHESIS OFF
set_global_assignment -name OPTIMIZE_HOLD_TIMING OFF
set_global_assignment -name OPTIMIZE_MULTI_CORNER_TIMING OFF
set_global_assignment -name FITTER_EFFORT "STANDARD FIT"


# Shatter rigid hard-macros so the Fitter can scatter logic to locked pins
set_global_assignment -name AUTO_CARRY_CHAINS OFF
set_global_assignment -name IGNORE_CARRY_BUFFERS ON
set_global_assignment -name IGNORE_CASCADE_BUFFERS ON

set_global_assignment -name SDC_FILE zx50_cpld_core.sdc
set_global_assignment -name VERILOG_FILE ../../git/Zx50/model_rev1/src/zx50_bus_arbiter.v
set_global_assignment -name VERILOG_FILE ../../git/Zx50/model_rev1/src/zx50_dma.v
set_global_assignment -name VERILOG_FILE ../../git/Zx50/model_rev1/src/zx50_mem_control.v


set_global_assignment -name MAX7000_DEVICE_IO_STANDARD TTL


# ==========================================
# VERIFIED KICAD PIN ASSIGNMENTS (U8 - ATF1508AS)
# ==========================================

# System Clocks & Control
set_location_assignment PIN_87 -to mclk
set_location_assignment PIN_90 -to zclk
set_location_assignment PIN_89 -to reset_n

# Z80 Backplane Control
set_location_assignment PIN_41 -to b_z80_m1_n
set_location_assignment PIN_96 -to int_n
set_location_assignment PIN_97 -to wait_n
set_location_assignment PIN_37 -to b_z80_mreq_n 
set_location_assignment PIN_40 -to b_z80_iorq_n
set_location_assignment PIN_33 -to b_z80_rd_n 
set_location_assignment PIN_35 -to b_z80_wr_n 

# Z80 Address Bus (A15 down to A0)
set_location_assignment PIN_21 -to z80_a[15]
set_location_assignment PIN_20 -to z80_a[14]
set_location_assignment PIN_19 -to z80_a[13]
set_location_assignment PIN_17 -to z80_a[12]
set_location_assignment PIN_16 -to z80_a[11]
set_location_assignment PIN_14 -to z80_a[10]
set_location_assignment PIN_13 -to z80_a[9]
set_location_assignment PIN_12 -to z80_a[8]
set_location_assignment PIN_10 -to z80_a[7]
set_location_assignment PIN_9 -to z80_a[6]
set_location_assignment PIN_8 -to z80_a[5]
set_location_assignment PIN_7 -to z80_a[4]
set_location_assignment PIN_6 -to z80_a[3]
set_location_assignment PIN_5 -to z80_a[2]
set_location_assignment PIN_2 -to z80_a[1]
set_location_assignment PIN_1 -to z80_a[0]

# Local Shared Data Bus (D7 down to D0)
set_location_assignment PIN_32 -to l_d[7]
set_location_assignment PIN_31 -to l_d[6]
set_location_assignment PIN_30 -to l_d[5]
set_location_assignment PIN_29 -to l_d[4]
set_location_assignment PIN_28 -to l_d[3]
set_location_assignment PIN_27 -to l_d[2]
set_location_assignment PIN_25 -to l_d[1]
set_location_assignment PIN_24 -to l_d[0]

# Shadow Bus Controls
set_location_assignment PIN_47 -to sh_en_n
set_location_assignment PIN_48 -to sh_rw_n
set_location_assignment PIN_46 -to sh_inc_n
set_location_assignment PIN_45 -to sh_stb_n
set_location_assignment PIN_49 -to sh_done_n
set_location_assignment PIN_50 -to sh_busy_n

# Transceiver Controls
set_location_assignment PIN_44 -to sh_c_dir
set_location_assignment PIN_23 -to z80_d_oe_n
set_location_assignment PIN_52 -to sh_data_oe_n
set_location_assignment PIN_22 -to d_dir

# Local Memory Address Bus (A10 down to A0)
set_location_assignment PIN_85 -to l_a[10]
set_location_assignment PIN_84 -to l_a[9]
set_location_assignment PIN_83 -to l_a[8]
set_location_assignment PIN_81 -to l_a[7]
set_location_assignment PIN_80 -to l_a[6]
set_location_assignment PIN_79 -to l_a[5]
set_location_assignment PIN_78 -to l_a[4]
set_location_assignment PIN_77 -to l_a[3]
set_location_assignment PIN_76 -to l_a[2]
set_location_assignment PIN_75 -to l_a[1]
set_location_assignment PIN_72 -to l_a[0]

# ATL Address Bus (A3 down to A0)
set_location_assignment PIN_56 -to atl_a[3]
set_location_assignment PIN_55 -to atl_a[2]
set_location_assignment PIN_54 -to atl_a[1]
set_location_assignment PIN_53 -to atl_a[0]

# ATL Data Bus (D7 down to D0)
set_location_assignment PIN_68 -to atl_d[7]
set_location_assignment PIN_67 -to atl_d[6]
set_location_assignment PIN_65 -to atl_d[5]
set_location_assignment PIN_64 -to atl_d[4]
set_location_assignment PIN_63 -to atl_d[3]
set_location_assignment PIN_61 -to atl_d[2]
set_location_assignment PIN_60 -to atl_d[1]
set_location_assignment PIN_58 -to atl_d[0]

# Memory Control Lines
set_location_assignment PIN_69 -to atl_we_n
set_location_assignment PIN_70 -to atl_oe_n
set_location_assignment PIN_71 -to atl_ce_n
set_location_assignment PIN_93 -to oe_n
set_location_assignment PIN_94 -to we_n

# CORRECTIONS FOR REV A HARDWARE:
set_location_assignment PIN_99 -to ram_ce0_n
set_location_assignment PIN_92 -to ram_ce1_n
set_location_assignment PIN_98 -to rom_ce2_n

set_location_assignment PIN_100 -to hb_led_n


set_global_assignment -name SYNTHESIS_SEED 3000
